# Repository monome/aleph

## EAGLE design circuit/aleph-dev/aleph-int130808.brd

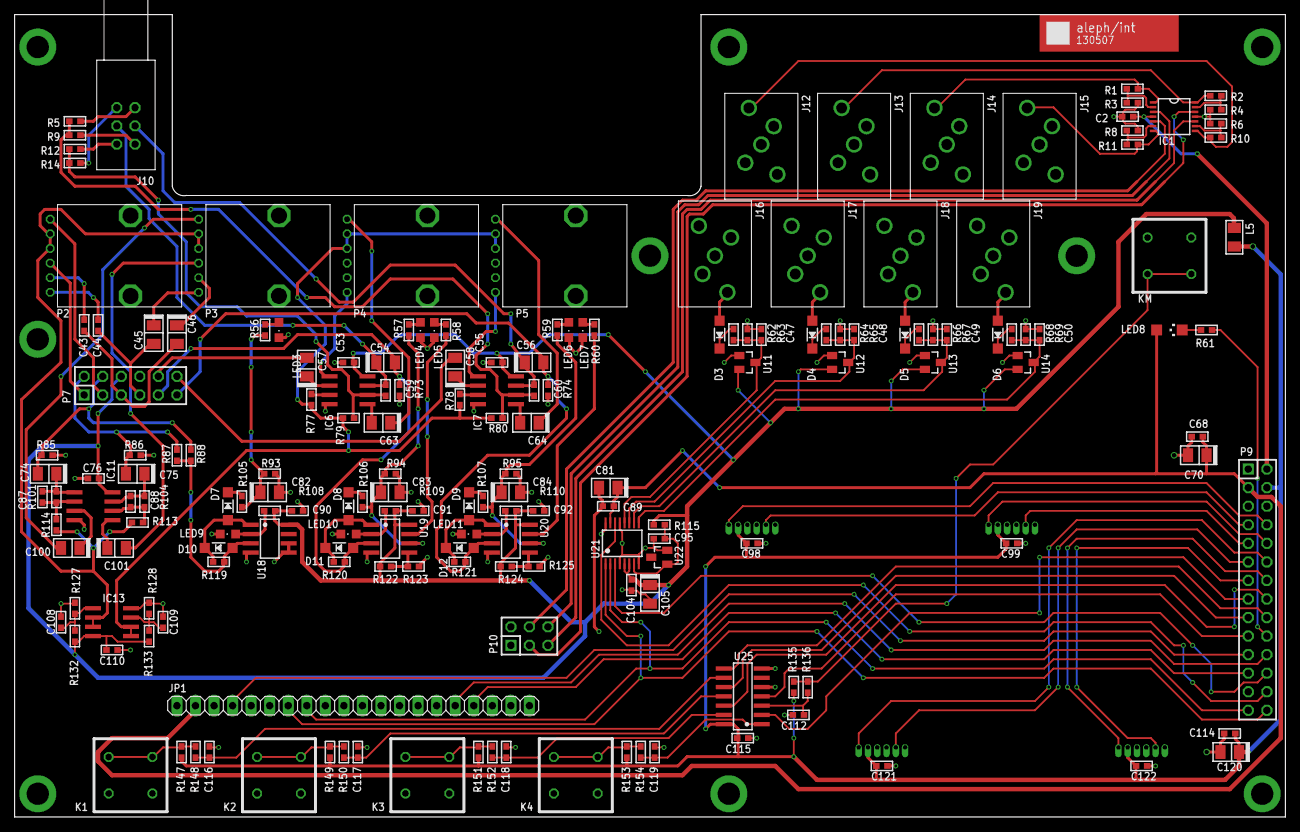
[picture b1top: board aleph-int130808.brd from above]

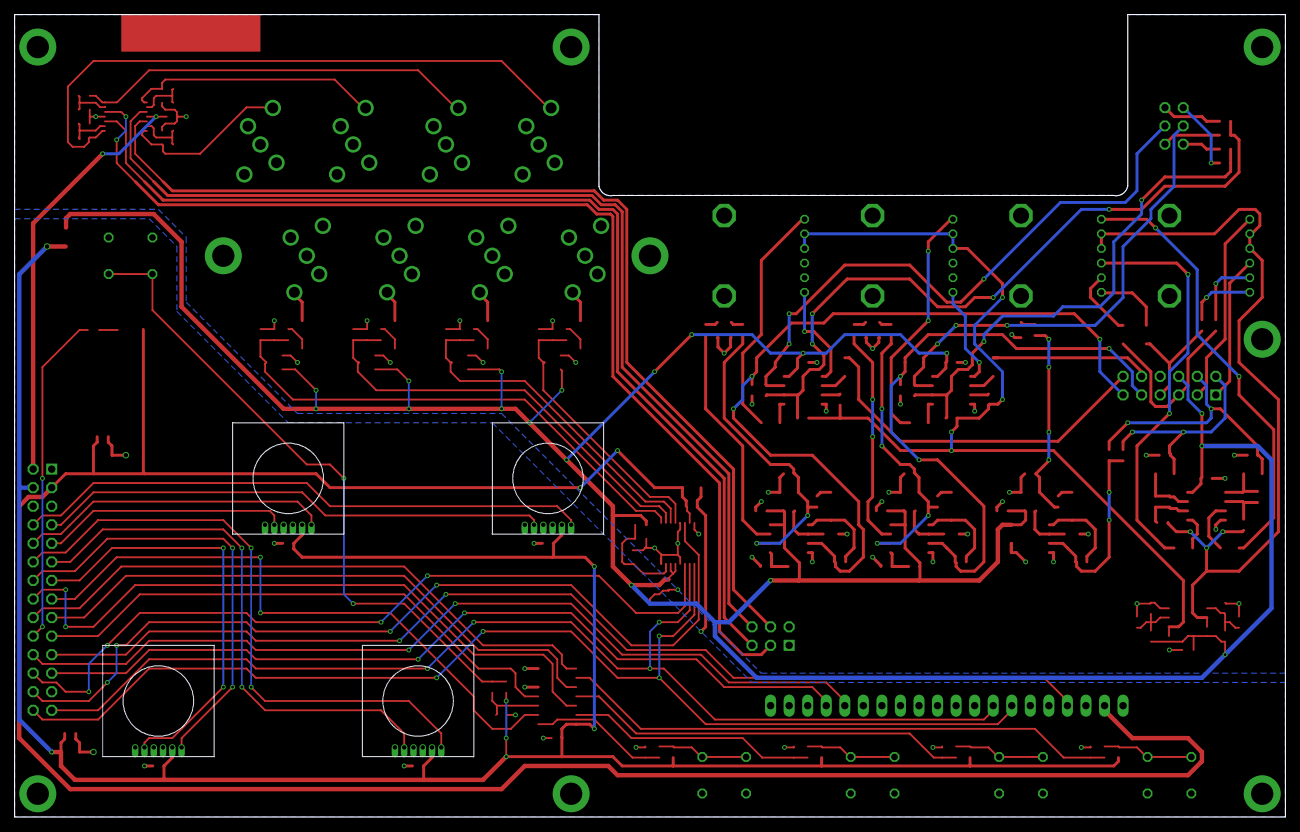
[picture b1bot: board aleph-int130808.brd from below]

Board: 4 copper layers, 174.0 x 109.9 mm, 196 parts (4 on the bottom side), 129 nets.

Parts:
C2, C53, C55, C68, C76, C89, C90, C91, C92, C95, C98, C99, C104, C108, C109, C110, C114, C115, C121, C122: 100n; C0603
C43, C44, C112, C116, C117, C118, C119: 1u; C0603
C45, C46, C54, C56, C57, C58, C63, C64, C70, C74, C75, C81, C82, C83, C84, C100, C101, C105, C120: 10u; C1206/T
C47, C48, C49, C50: 10n; C0603
C59, C60, C87, C88: 100p; C0603
D3, D4, D5, D6, D7, D8, D9, D10, D11, D12: 1N4148W-7; SOD123
E1, E2, E3, E4: BOURNS-EM14
H4, H5, H6, H7, H8, H9, H13, H14, H15: MOUNT440; 120-PAD-NS
IC1: AD8567; TSSOP14
IC6, IC7, IC11, IC13: AD8607R; SO8
J10: PHA2U
J12, J13, J14, J15, J16, J17, J18, J19: STX-3680
JP1: OLED; 1X20
K1, K2, K3, K4: PVA1
KM: PVA1
L5: 600; L1206
LED3, LED4, LED5, LED6, LED7, LED9, LED10, LED11: CHIPLED_0805
LED8: CHIPLED_1206
P2, P3, P4, P5: EVJ-POT
P7: M-2X06-DIL-100; DIL-100-2X06
P9: M-2X14-DIL-100; DIL-100-2X14
P10: M-2X03-DIL-100; DIL-100-2X03
R1, R2, R3, R4, R5, R6, R8, R10, R11, R14, R62, R63, R64, R65, R66, R67, R68, R69, R93, R94, R95, R101, R104, R108, R109, R110: 10k; R0603
R9, R12: 47k; R0603
R56, R57, R58, R59, R60, R105, R106, R107: 270; R0603
R61: 150; R0603
R73, R74, R85, R86, R123, R125, R127, R128, R132, R133: 100k; R0603
R77, R78, R119, R120, R121: 470k; R0603
R79, R80, R113, R114: 4k7; R0603
R87, R88, R115: 1k; R0603
R122, R124: 56k; R0603
R135, R147, R149, R151, R153: 82k; R0603
R136, R148, R150, R152, R154: 18k; R0603
REF-OLED: NHD-2.7
U11, U12, U13, U14: BAS70-04; SOT23
U18, U19, U20: TL072D; SO08
U21: AD7923; TSSOP16
U22: LM4040M3; SOT23
U25: 74HC14D; SO14

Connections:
+3V3: C68.2, C70.+, C81.+, C89.2, JP1.2, LED8.A, P9.3, U21.15
+5V: C98.2, C99.2, C114.2, C115.2, C120.+, C121.2, C122.2, E1.P$5, E2.P$5, E3.P$5, E4.P$5, L5.2, P9.4, R135.1, R147.1, R149.1, R151.1, R153.1, U25.14
+5VA: C53.2, C55.2, C76.2, C90.2, C91.2, C92.2, C104.2, C105.+, C110.2, IC6.8, IC7.8, IC11.8, IC13.8, L5.1, P7.6, R108.2, R109.2, R110.2, R115.1, R122.1, R124.1, R132.2, R133.2, U11.2, U12.2, U13.2, U14.2, U18.8, U19.8, U20.8, U21.5, U21.6
+12V: C2.1, IC1.4, P9.2
AGND: C2.2, C47.2, C48.2, C49.2, C50.2, C53.1, C55.1, C76.1, C82.-, C83.-, C84.-, C90.1, C91.1, C92.1, C95.1, C104.1, C105.-, C108.1, C109.1, C110.1, IC1.11, IC6.4, IC7.4, IC11.4, IC13.4, J12.5, J13.5, J14.5, J15.5, J16.3, J16.5, J17.3, J17.5, J18.3, J18.5, J19.3, J19.5, LED3.C, LED4.C, LED5.C, LED6.C, LED7.C, LED9.C, LED10.C, LED11.C, P7.8, P10.1, P10.2, R3.2, R4.2, R6.2, R8.2, R63.2, R65.2, R67.2, R69.2, R73.1, R74.1, R85.1, R86.1, R93.2, R94.2, R95.2, R123.2, R125.2, R127.1, R128.1, U11.1, U12.1, U13.1, U14.1, U18.4, U18.5, U18.6, U19.4, U20.4, U21.4, U21.8, U21.13, U21.16, U22.2
CVOUT1^: IC1.3, P10.6
CVOUT2^: IC1.5, P10.4
CVOUT3^: IC1.10, P10.5
CVOUT4^: IC1.12, P10.3
ENC0A^: E1.P$2, P9.13
ENC0B^: E1.P$6, P9.14
ENC1A^: E2.P$2, P9.11
ENC1B^: E2.P$6, P9.12
ENC2A^: E4.P$2, P9.9
ENC2B^: E4.P$6, P9.10
ENC3A^: E3.P$2, P9.7
ENC3B^: E3.P$6, P9.8
GAINL-1: C54.+, C59.1, IC6.7, J10._0
GAINL-2: C59.2, IC6.6, R12.1, R14.1, R79.2
GAINR-1: C56.+, C60.1, IC7.7, J10.0
GAINR-2: C60.2, IC7.6, R5.1, R9.1, R80.2
GND: C68.1, C70.-, C81.-, C89.1, C98.1, C99.1, C112.1, C114.1, C115.1, C116.1, C117.1, C118.1, C119.1, C120.-, C121.1, C122.1, E1.P$1, E2.P$1, E3.P$1, E4.P$1, JP1.1, JP1.5, JP1.6, JP1.10, JP1.11, JP1.12, JP1.13, JP1.14, JP1.19, JP1.20, K1.2, K1.3, K2.2, K2.3, K3.2, K3.3, K4.2, K4.3, KM.2, KM.3, P9.1, P9.5, P9.6, U25.5, U25.7
HPL^: P2.4, P7.1
HPR^: P2.1, P7.3
IN1L-J^: C57.-, P7.10
IN1L^: C54.-, D11.A, P7.9, R73.2, R120.2, U19.3
IN1R-J^: C58.-, P7.12
IN1R^: C56.-, D12.A, P7.11, R74.2, R121.2, U20.3
IN-VREF: IC13.1, IC13.2, P4.2, P4.3, P5.2, P5.3, R77.1, R78.1, R79.1, R80.1
KEY0^: P9.18, U25.8
KEY1^: P9.17, U25.10
KEY2^: P9.16, U25.12
KEY3^: P9.15, U25.2
MODE-KEY^: P9.19, U25.4
MODE-LED^: P9.20, R61.1
unnamed: IC1.2, R1.2, R3.1
unnamed: K1.1, K1.4, R147.2, R148.1
unnamed: C116.2, R148.2, U25.9
unnamed: K2.1, K2.4, R149.2, R150.1
unnamed: C117.2, R150.2, U25.11
unnamed: LED8.C, R61.2
unnamed: K3.1, K3.4, R151.2, R152.2
unnamed: C118.2, R152.1, U25.13
unnamed: K4.1, K4.4, R153.2, R154.2
unnamed: C119.2, R154.1, U25.1
unnamed: C45.+, P3.6
unnamed: D3.A, J16.4
unnamed: D4.C, R64.2
unnamed: D3.C, R62.2
unnamed: D5.C, R66.2
unnamed: C46.+, P3.5
unnamed: D4.A, J17.4
unnamed: KM.1, KM.4, R135.2, R136.2
unnamed: D6.C, R68.2
unnamed: C100.-, P3.1
unnamed: D5.A, J18.4
unnamed: C112.2, R136.1, U25.3
unnamed: C101.+, IC11.5
unnamed: D6.A, J19.4
unnamed: IC1.1, J14.4, R1.1
unnamed: C95.2, R115.2, U21.7, U22.1
unnamed: C75.+, C88.2, IC11.7, R104.2
unnamed: C88.1, IC11.6, R104.1, R113.2
unnamed: C101.-, P3.4
unnamed: C100.+, IC11.3
unnamed: C74.+, C87.2, IC11.1, R101.2
unnamed: C87.1, IC11.2, R101.1, R114.2
unnamed: C48.1, R64.1, R65.1, U12.3, U21.11
unnamed: C49.1, R66.1, R67.1, U13.3, U21.10
unnamed: C50.1, R68.1, R69.1, U14.3, U21.9
unnamed: C47.1, R62.1, R63.1, U11.3, U21.12
unnamed: IC1.6, R8.1, R11.2
unnamed: IC1.9, R6.1, R10.2
unnamed: IC1.13, R2.2, R4.1
unnamed: IC1.8, J12.4, R10.1
unnamed: IC1.14, J13.4, R2.1
unnamed: IC1.7, J15.4, R11.1
unnamed: C43.1, P2.5
unnamed: C44.1, P2.6
unnamed: C109.2, IC13.3, R128.2, R133.1
unnamed: IC6.3, R77.2
unnamed: IC6.1, P4.6
unnamed: C63.-, IC6.5
unnamed: D8.A, D11.C, R120.1, U19.1
unnamed: C108.2, IC13.5, R127.2, R132.1
unnamed: C57.+, IC6.2
unnamed: C63.+, P4.1
unnamed: D8.C, R106.2
unnamed: C83.+, R57.1, R94.1, R106.1, U19.6
unnamed: LED10.A, R109.1, U19.2
unnamed: IC7.3, R78.2
unnamed: J10._2, R12.2
unnamed: IC7.1, P5.6
unnamed: LED4.A, R57.2
unnamed: LED5.A, R58.2
unnamed: J10._1, R14.2
unnamed: J10.2, R9.2
unnamed: J10.1, R5.2
unnamed: R58.1, U19.7
unnamed: R122.2, R123.1, U19.5
unnamed: C64.-, IC7.5
unnamed: C58.+, IC7.2
unnamed: C64.+, P5.1
unnamed: D9.A, D12.C, R121.1, U20.1
unnamed: D9.C, R107.2
unnamed: C84.+, R59.1, R95.1, R107.1, U20.6
unnamed: LED11.A, R110.1, U20.2
unnamed: LED6.A, R59.2
unnamed: LED7.A, R60.2
unnamed: R60.1, U20.7
unnamed: R124.2, R125.1, U20.5
unnamed: D10.A, R87.1, R88.1, R119.2, U18.3
unnamed: D7.A, D10.C, R119.1, U18.1
unnamed: D7.C, R105.2
unnamed: C82.+, R56.1, R93.1, R105.1
unnamed: LED9.A, R108.1, U18.2
unnamed: LED3.A, R56.2
OLED-DC^: JP1.4, P9.21
OLED-RES^: JP1.16, P9.22
OUT1L-J^: C75.-, P7.2, R86.2, R87.2
OUT1L^: C43.2, C46.-, P7.5
OUT1R-J^: C74.-, P7.4, R85.2, R88.2
OUT1R^: C44.2, C45.-, P7.7
OUT-VREF: IC13.6, IC13.7, P2.2, P2.3, P3.2, P3.3, R113.1, R114.1
SPI1-CS0^: JP1.17, P9.23
SPI1-CS1^: P9.24, U21.3
SPI1-MISO^: P9.26, U21.14
SPI1-MOSI^: JP1.8, P9.27, U21.2
SPI1-SCK^: JP1.7, P9.28, U21.1

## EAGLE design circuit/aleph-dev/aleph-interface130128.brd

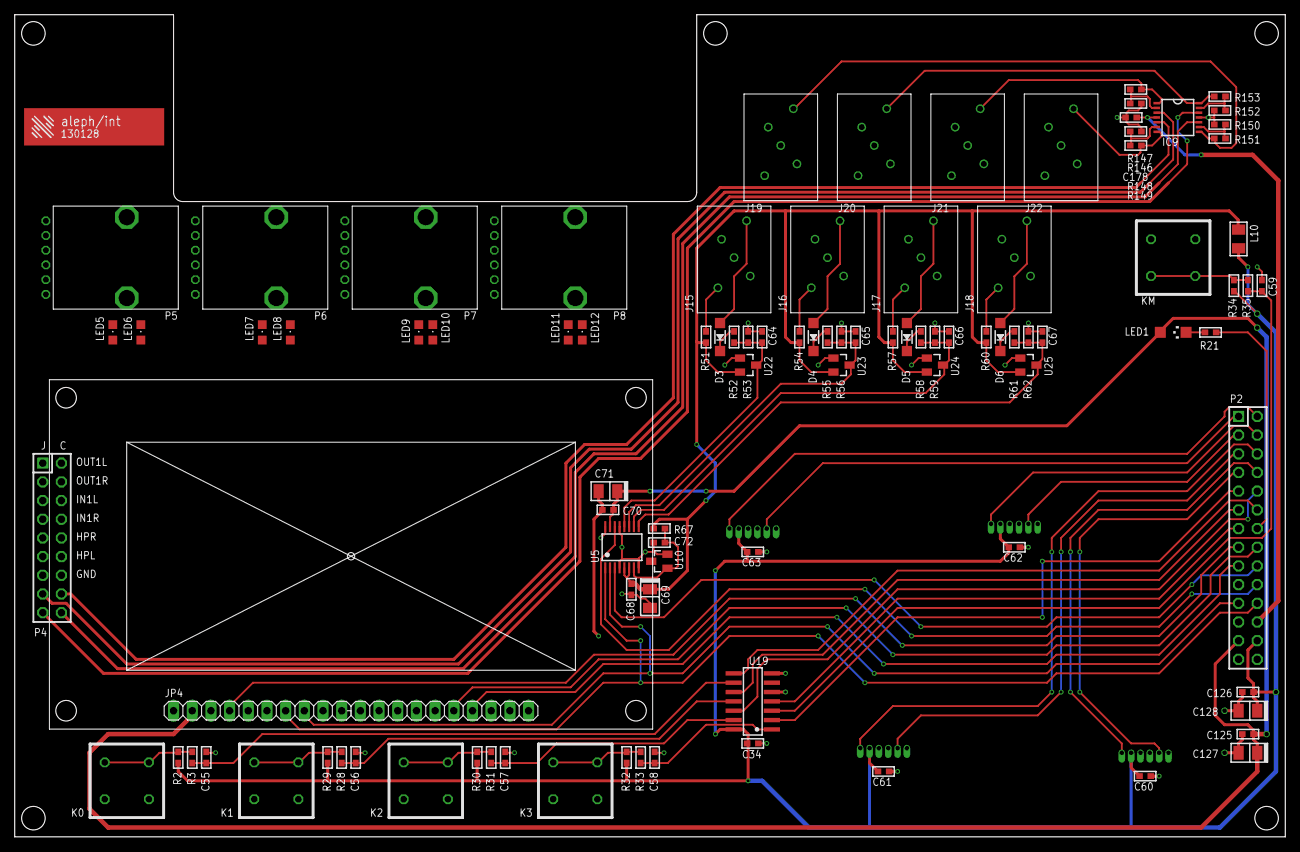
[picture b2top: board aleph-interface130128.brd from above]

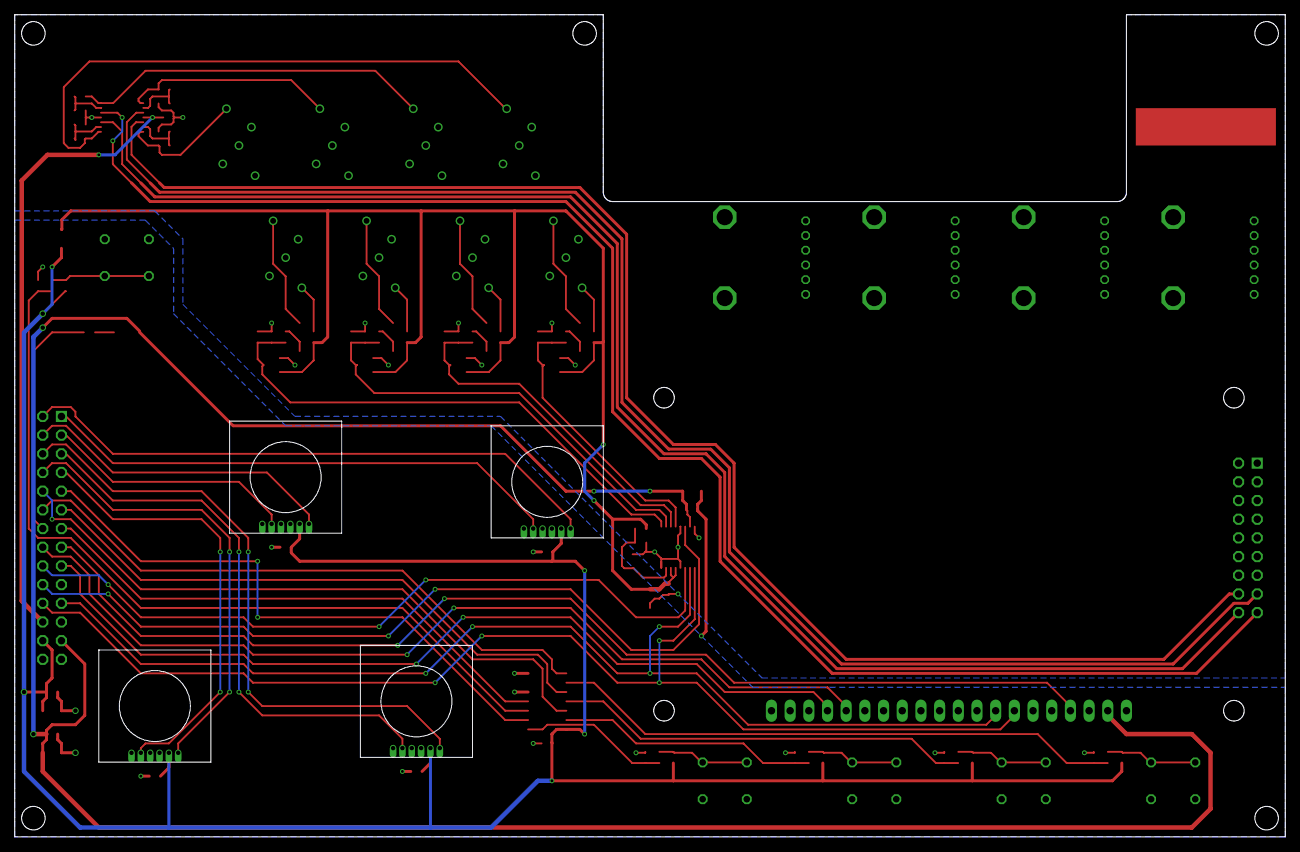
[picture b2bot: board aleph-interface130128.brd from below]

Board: 4 copper layers, 172.7 x 111.8 mm, 103 parts (4 on the bottom side), 67 nets.

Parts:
C34, C60, C61, C62, C63, C68, C70, C72, C125, C126, C178: 100n; C0603
C55, C56, C57, C58, C59: 1u; C0603
C64, C65, C66, C67: 10n; C0603
C69, C71, C127, C128: 10u; C1206/T
D3, D4, D5, D6: 1N4148W-7; SOD123
IC9: AD8567; TSSOP14
J15, J16, J17, J18, J19, J20, J21, J22: STX-3680
JP4: OLED; 1X20
K0, K1, K2, K3: PVA1
KM: PVA1
L10: 600; L1206
LED1: CHIPLED_1206
LED5, LED6, LED7, LED8, LED9, LED10, LED11, LED12: CHIPLED_0805
P2: M-2X14-DIL-100; DIL-100-2X14
P4: M-2X09-DIL-100; DIL-100-2X09
P5, P6, P7, P8: EVJ-POT
R2, R29, R30, R32, R34: 82k; R0603
R3, R28, R31, R33, R35: 18k; R0603
R21: 150; R0603
R51, R52, R53, R54, R55, R56, R57, R58, R59, R60, R61, R62, R146, R147, R148, R149, R150, R151, R152, R153: 10k; R0603
R67: 1k; R0603
U5: AD7923; TSSOP16
U10: LM4040M3; SOT23
U19: 74HC14D; SO14
U22, U23, U24, U25: BAS70-04; SOT23
U$2, U$3, U$4, U$5: BOURNS-EM14
U$10: NHD-2.7

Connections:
+3V3: C70.2, C71.+, C125.2, C127.+, JP4.2, LED1.A, P2.25, U5.15
+5V: C34.2, C60.2, C61.2, C62.2, C63.2, C126.2, C128.+, L10.2, P2.26, R2.1, R29.1, R30.1, R32.1, R34.1, U19.14, U$2.P$5, U$3.P$5, U$4.P$5, U$5.P$5
+5VA: C68.2, C69.+, L10.1, R51.2, R54.2, R57.2, R60.2, R67.1, U5.5, U5.6, U22.2, U23.2, U24.2, U25.2
+12V: C178.1, IC9.4, P2.24
AGND: C64.2, C65.2, C66.2, C67.2, C68.1, C69.-, C72.1, C178.2, IC9.11, J15.3, J15.5, J16.3, J16.5, J17.3, J17.5, J18.3, J18.5, J19.5, J20.5, J21.5, J22.5, P4.13, P4.14, R53.2, R56.2, R59.2, R62.2, R146.2, R148.2, R150.2, R152.2, U5.4, U5.8, U5.13, U5.16, U10.2, U22.1, U23.1, U24.1, U25.1
CVOUT1^: IC9.3, P4.15
CVOUT2^: IC9.5, P4.16
CVOUT3^: IC9.10, P4.18
CVOUT4^: IC9.12, P4.17
ENC0A^: P2.7, U$2.P$2
ENC0B^: P2.8, U$2.P$6
ENC1A^: P2.5, U$3.P$2
ENC1B^: P2.6, U$3.P$6
ENC2A^: P2.3, U$4.P$2
ENC2B^: P2.4, U$4.P$6
ENC3A^: P2.1, U$5.P$2
ENC3B^: P2.2, U$5.P$6
GND: C34.1, C55.1, C56.1, C57.1, C58.1, C59.1, C60.1, C61.1, C62.1, C63.1, C70.1, C71.-, C125.1, C126.1, C127.-, C128.-, JP4.1, JP4.5, JP4.6, JP4.10, JP4.11, JP4.12, JP4.13, JP4.14, JP4.19, JP4.20, K0.2, K0.3, K1.2, K1.3, K2.2, K2.3, K3.2, K3.3, KM.2, KM.3, P2.23, P2.27, P2.28, U19.5, U19.7, U$2.P$1, U$3.P$1, U$4.P$1, U$5.P$1
KEY0^: P2.12, U19.8
KEY1^: P2.11, U19.10
KEY2^: P2.10, U19.12
KEY3^: P2.9, U19.2
MODE-KEY^: P2.13, U19.4
MODE-LED^: P2.14, R21.1
unnamed: IC9.2, R146.1, R147.2
unnamed: K0.1, K0.4, R2.2, R3.1
unnamed: C55.2, R3.2, U19.9
unnamed: K1.1, K1.4, R28.1, R29.2
unnamed: C56.2, R28.2, U19.11
unnamed: LED1.C, R21.2
unnamed: K2.1, K2.4, R30.2, R31.2
unnamed: C57.2, R31.1, U19.13
unnamed: K3.1, K3.4, R32.2, R33.2
unnamed: C58.2, R33.1, U19.1
unnamed: J17.1, R57.1
unnamed: D3.A, J15.4
unnamed: D4.C, R55.2
unnamed: D3.C, R52.2
unnamed: D5.C, R58.2
unnamed: J16.1, R54.1
unnamed: D4.A, J16.4
unnamed: KM.1, KM.4, R34.2, R35.2
unnamed: D6.C, R61.2
unnamed: J15.1, R51.1
unnamed: D5.A, J17.4
unnamed: C59.2, R35.1, U19.3
unnamed: J18.1, R60.1
unnamed: D6.A, J18.4
unnamed: IC9.1, J21.4, R147.1
unnamed: C72.2, R67.2, U5.7, U10.1
unnamed: C65.1, R55.1, R56.1, U5.11, U23.3
unnamed: C66.1, R58.1, R59.1, U5.10, U24.3
unnamed: C67.1, R61.1, R62.1, U5.9, U25.3
unnamed: C64.1, R52.1, R53.1, U5.12, U22.3
unnamed: IC9.6, R148.1, R149.2
unnamed: IC9.9, R150.1, R151.2
unnamed: IC9.13, R152.1, R153.2
unnamed: IC9.8, J19.4, R151.1
unnamed: IC9.14, J20.4, R153.1
unnamed: IC9.7, J22.4, R149.1
OLED-DC^: JP4.4, P2.15
OLED-RES^: JP4.16, P2.16
SPI1-CS0^: JP4.17, P2.17
SPI1-CS1^: P2.18, U5.3
SPI1-MISO^: P2.20, U5.14
SPI1-MOSI^: JP4.8, P2.21, U5.2
SPI1-SCK^: JP4.7, P2.22, U5.1

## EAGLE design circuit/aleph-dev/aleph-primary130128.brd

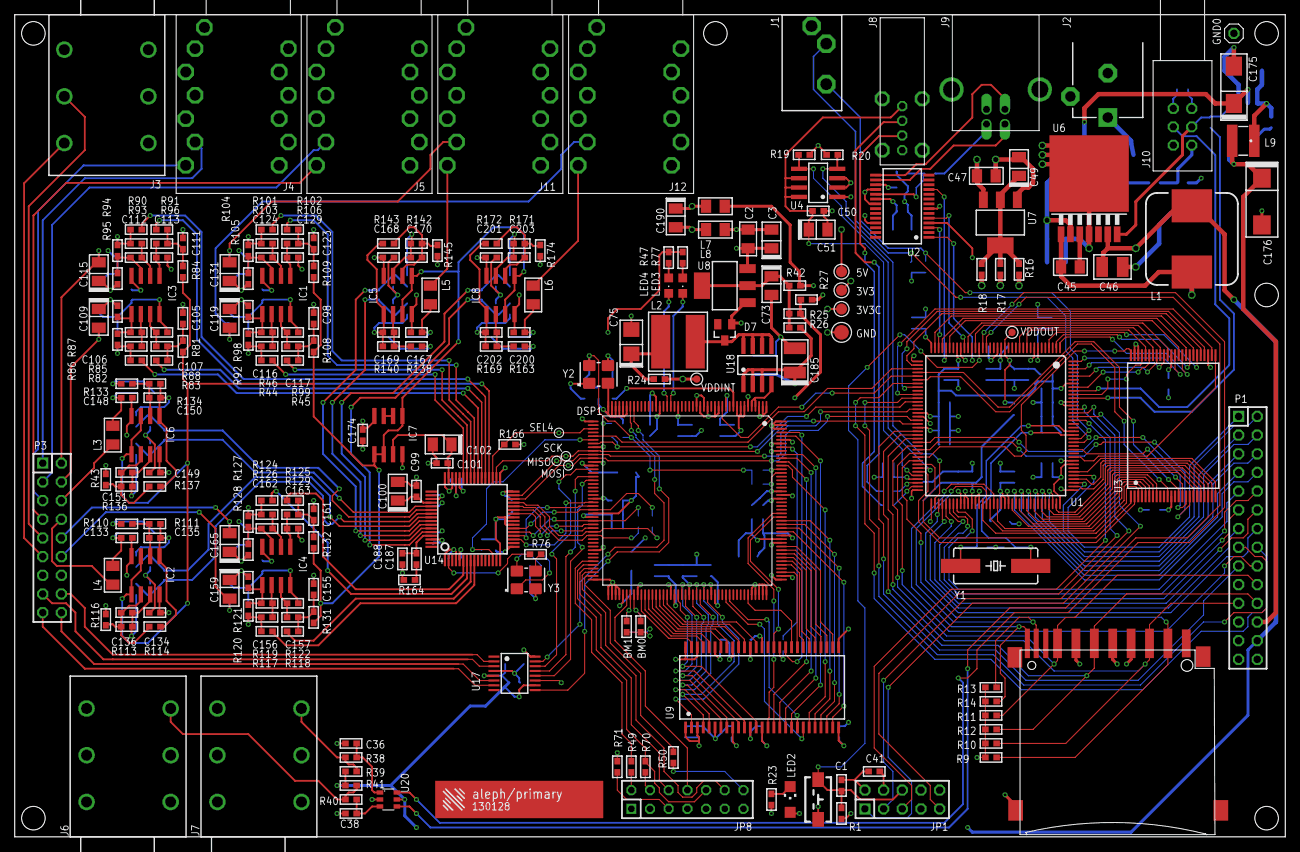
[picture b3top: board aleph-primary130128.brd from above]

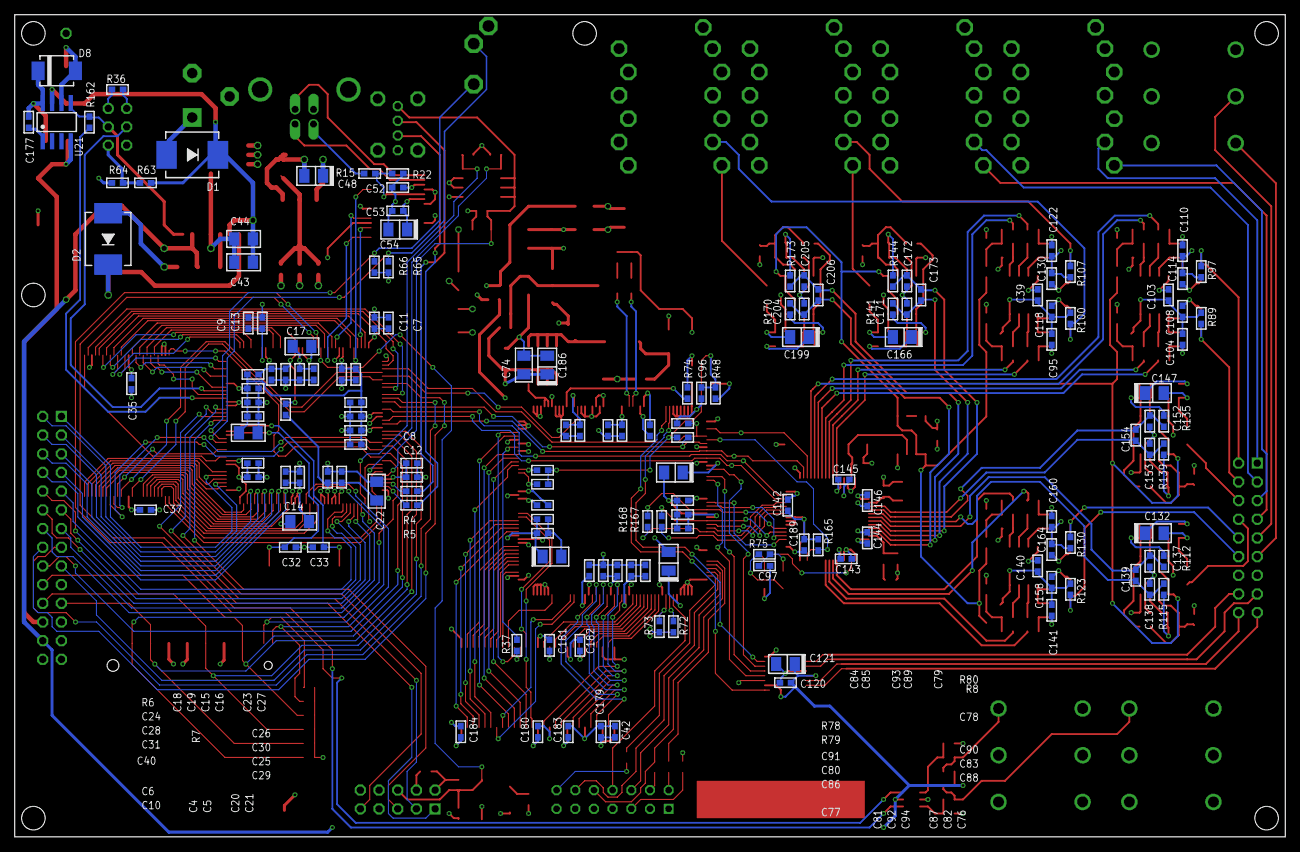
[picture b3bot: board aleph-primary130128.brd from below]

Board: 4 copper layers, 172.7 x 111.8 mm, 374 parts (152 on the bottom side), 317 nets.

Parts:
3V3, 3V3C, 5V: TPS-SMD-15R; SMD-15R
BM0: 0; R0603
BM1: DNP; R0603
C1, C4, C6, C7, C8, C9, C16, C31, C39, C41, C50, C52, C53, C79, C80, C81, C82, C83, C84, C89, C90, C91, C92, C99, C101, C103, C120, C134, C140, C142, C143, C144, C145, C146, C149, C168, C174, C189, C201: 100n; C0603
C2, C47, C74: 100n; C1206
C3, C48, C49, C73, C76, C77, C78, C102, C109, C115, C119, C121, C131, C159, C165, C186, C190: 10u; C1206/T
C5, C10, C11, C12, C13, C15, C21, C27, C28, C29, C30: 33n; C0603
C14, C17: 4.7u; C1206
C18: 2.2u; C0603
C19: 470p; C0603
C20, C23, C24, C25, C26: 2.7n; C0603
C22, C40: 2.2u; C1206
C32, C33: 18p; C0603
C35, C37, C42, C85, C86, C87, C88, C93, C94, C96, C97, C177, C179, C180, C181, C182, C183, C184: 10n; C0603
C36, C38: 1u; C0603
C43: 22u; C1206
C44: 470n; C1206
C45: 10n; C1206
C46: 47u; C3225
C51, C54, C132, C147, C166, C199: 4.7u; C1206/T
C75: 100u; C3528/T
C95, C104, C110, C122, C141, C160: 330p; C0603
C98, C105, C111, C123, C155, C161: 680p; C0603
C100: 47u; C1206/T
C106, C112, C116, C124, C133, C139, C148, C154, C156, C162, C167, C173, C200, C206: 100p; C0603
C107, C113, C117, C129, C157, C163: 220p; C0603
C108, C114, C118, C130, C158, C164: 2200p; C0603
C135, C136, C150, C151, C169, C170, C202, C203: 120p; C0603
C137, C138, C152, C153, C171, C172, C204, C205: 1n; C0603
C175: 15u; C6032/T
C176: 68u; C7343/T
C185: 100u; C1210/T
C187: 5600p; C0603
C188: 390p; C0603
D1, D2: MBRS360T3; SMC
D7: zhcs1000; SOT23
D8: MBRS130LT3; SMB403A
DSP1: BF533; LQFP176
GND: TPS-SMD-20R; SMD-20R
GND0: 1X01
IC1, IC2, IC3, IC4, IC5, IC6, IC8: AD8606; SO8
IC7: AD8607R; SO8
J1: SJ1-3533NG
J2: PJ-102AH/BH; PJ-102XH
J3, J6, J7: STEREOSW2GND; NEUTRIK-NRJ6HM-1
J4, J5, J11, J12: NSJ12HF
J8: USBA-VERT
J9: USB_B
J10: PHA2U
JP1: AVR-JTAG; AVR-JTAG-10
JP8: JPQ-07-100; JPQ-07
L1: MSS1278
L2: SRR6038-100Y; SRR6038
L3, L4, L5, L6, L7, L8: 600; L1206
L9: LPS4018-68uh; LPS4018
LED2: CHIPLED_1206
LED3, LED4: CHIPLED_0805
P1: M-2X14-DIL-100; DIL-100-2X14
P3: M-2X09-DIL-100; DIL-100-2X09
R1, R22, R48, R65, R66, R72, R73, R75, R78, R79, R80, R165: 10k; R0603
R4, R5: 39; R0603
R6, R7, R16, R17, R18, R24, R25, R26, R42, R49, R50, R167, R168: 0; R0603
R8, R9, R10, R11, R12, R13, R14, R36, R64, R162, R166: 100k; R0603
R15: 4.7k; R0603
R19, R20: 47k; R0603
R23, R47, R77: 150; R0603
R27: 3.32k; R0603
R37: 22; R0603
R38, R40: 18k; R0603
R39, R41: 82k; R0603
R43, R116, R145, R174: 750k; R0603
R44, R82, R90, R101, R117, R124: 11k; R0603
R45, R83, R86, R91, R92, R94, R102, R104, R118, R120, R125, R127: 5k49; R0603
R46, R85, R93, R103, R119, R126: 3k32; R0603
R63: 330k; R0603
R70, R71: 4k7; R0603
R74, R76: 33; R0603
R81, R84, R108, R109, R131, R132: 2k74; R0603
R87, R95, R98, R105, R121, R128: 604; R0603
R88, R96, R99, R106, R122, R129: 1k65; R0603
R89, R97, R100, R107, R123, R130: 49k9; R0603
R110, R111, R113, R114, R133, R134, R136, R137, R138, R140, R142, R143, R163, R169, R171, R172: 5k76; R0603
R112, R115, R135, R139, R141, R144, R170, R173: 237; R0603
R164: 562; R0603
U1: AT32UC3A0512; LQFP144
U2: FT232RL; SSOP28
U3: CY62167EV30-Z; TSOP48
U4: TPS2020; SO08
U6: LM2678; TO263-7
U7, U8: ADP3339; SOT223
U9: MT48LC32M16A2tg-75; TSOP54
U14: AD1939; SQFP-S-10X10-64
U17: AD5686R; TSSOP16
U18: FDS9431A; SO08
U20: SN74LVC2G14; SOT23-6
U21: LM2674; SO08
U$1: PANASONIC-EVQ
U$6: SDMMC06132; 06132
VDDINT: TPS-SMD-10R; SMD-10R
VDDOUT: TPS-SMD-10R; SMD-10R
Y1: 12mhz; HC49UP@1
Y2: ASFL1-27mhz; ASFL1
Y3: ASFL1-12.288mhz; ASFL1

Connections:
+3V3: 3V3.TP, C35.1, C37.1, C41.1, JP1.4, LED2.A, P1.25, R1.2, R9.2, R10.2, R11.2, R12.2, R13.2, R14.2, R18.1, R65.1, R66.1, U2.4, U3.12, U3.37, U$6.4
+3V3A: C39.2, C103.2, C134.2, C140.2, C143.1, C144.1, C145.1, C146.1, C149.2, C168.2, C174.2, C188.1, C190.+, C201.2, IC1.8, IC2.8, IC3.8, IC4.8, IC5.8, IC6.8, IC7.8, IC8.8, L7.1, R164.2, U14.5, U14.45, U14.51, U14.62
+3V3C: 3V3C.TP, C42.2, C96.1, C97.1, C142.1, C179.2, C180.2, C181.2, C182.2, C183.2, C184.2, C189.1, L7.2, R8.2, R42.1, R47.2, R48.2, R71.1, R72.2, R73.2, R75.2, R77.2, R78.2, R79.2, R166.1, U9.1, U9.3, U9.9, U9.14, U9.27, U9.43, U9.49, U14.17, U14.32, U17.11, Y2.4, Y3.4
+5V: 5V.TP, C2.2, C3.+, C46.1, C47.2, C48.+, C53.2, C54.+, C120.1, C121.+, L1.2, P1.26, R19.2, R20.2, R39.1, R41.1, U2.20, U4.2, U4.3, U6.6, U7.3, U8.3, U17.5, U17.10, U20.5
+12V: C176.+, L9.2, P1.24, U21.4
A-A1: U1.118, U3.25
A-A2: U1.114, U3.24
A-A3: U1.112, U3.23
A-A4: U1.110, U3.22
A-A5: U1.107, U3.21
A-A6: U1.105, U3.20
A-A7: U1.103, U3.19
A-A8: U1.101, U3.18
A-A9: U1.99, U3.8
A-A10: U1.97, U3.7
A-A11: U1.95, U3.6
A-A12: U1.91, U3.5
A-A13: U1.89, U3.4
A-A14: U1.87, U3.3
A-A15: U1.67, U3.2
A-A16: U1.65, U3.1
A-A17: U1.63, U3.48
A-A18: U1.61, U3.17
A-A19: U1.59, U3.16
A-D0: U1.38, U3.29
A-D1: U1.35, U3.31
A-D2: U1.33, U3.33
A-D3: U1.31, U3.35
A-D4: U1.26, U3.38
A-D5: U1.24, U3.40
A-D6: U1.12, U3.42
A-D7: U1.10, U3.44
A-D8: U1.4, U3.30
A-D9: U1.2, U3.32
A-D10: U1.1, U3.34
A-D11: U1.144, U3.36
A-D12: U1.142, U3.39
A-D13: U1.140, U3.41
A-D14: U1.137, U3.43
A-D15: U1.135, U3.45
A-RESET: C1.1, JP1.6, R1.1, U1.23, U$1.2
A-TCK: JP1.1, U1.129
A-TDI: JP1.9, U1.131
A-TDO: JP1.3, U1.130
A-TMS: JP1.5, U1.128
ABE0_: DSP1.P$151, U9.15
ABE1_: DSP1.P$150, U9.39
AD1939_RESET: DSP1.P$50, R165.1, U14.14
AGND: C39.1, C95.1, C98.2, C99.1, C100.-, C101.1, C102.-, C103.1, C104.1, C105.2, C107.1, C108.1, C110.1, C111.2, C113.1, C114.1, C117.1, C118.1, C120.2, C121.-, C122.1, C123.2, C129.1, C130.1, C133.1, C134.1, C137.2, C138.1, C140.1, C141.1, C143.2, C144.2, C145.2, C146.2, C148.1, C149.1, C152.2, C153.1, C155.2, C157.1, C158.1, C160.1, C161.2, C163.1, C164.1, C167.1, C168.1, C171.2, C172.1, C174.1, C190.-, C200.1, C201.1, C204.2, C205.1, IC1.4, IC2.4, IC3.4, IC4.4, IC5.4, IC6.4, IC7.4, IC8.4, J3.RN, J3.S, J3.TN, J4.G, J4.RNB, J4.RNT, J4.SB, J4.SNB, J4.SNT, J4.ST, J4.TNB, J4.TNT, J5.G, J5.RNB, J5.RNT, J5.SB, J5.SNB, J5.SNT, J5.ST, J5.TNB, J5.TNT, J11.RNB, J11.RNT, J11.SB, J11.SNB, J11.SNT, J11.ST, J11.TNB, J11.TNT, J12.G, J12.RNB, J12.RNT, J12.SB, J12.SNB, J12.SNT, J12.ST, J12.TNB, J12.TNT, L8.1, P3.13, P3.14, R43.2, R89.2, R97.2, R100.2, R107.2, R116.2, R123.2, R130.2, R145.2, R174.2, U14.1, U14.4, U14.44, U14.46, U14.48, U17.4, U17.16
B-A1: DSP1.P$149, U9.23
B-A2: DSP1.P$148, U9.24
B-A3: DSP1.P$147, U9.25
B-A4: DSP1.P$146, U9.26
B-A5: DSP1.P$142, U9.29
B-A6: DSP1.P$141, U9.30
B-A7: DSP1.P$140, U9.31
B-A8: DSP1.P$139, U9.32
B-A9: DSP1.P$138, U9.33
B-A10: DSP1.P$137, U9.34
B-A12: DSP1.P$135, U9.35
B-A13: DSP1.P$127, U9.36
B-A18: DSP1.P$122, U9.20
B-A19: DSP1.P$121, U9.21
B-D0: DSP1.P$116, U9.2
B-D1: DSP1.P$115, U9.4
B-D2: DSP1.P$114, U9.5
B-D3: DSP1.P$113, U9.7
B-D4: DSP1.P$112, U9.8
B-D5: DSP1.P$110, U9.10
B-D6: DSP1.P$109, U9.11
B-D7: DSP1.P$108, U9.13
B-D8: DSP1.P$105, U9.42
B-D9: DSP1.P$104, U9.44
B-D10: DSP1.P$103, U9.45
B-D11: DSP1.P$102, U9.47
B-D12: DSP1.P$101, U9.48
B-D13: DSP1.P$100, U9.50
B-D14: DSP1.P$99, U9.51
B-D15: DSP1.P$98, U9.53
B-HWAIT: DSP1.P$49, R80.2, U1.39
B-MISO: DSP1.P$54, U1.50, U14.31
B-MOSI: DSP1.P$55, U1.53, U14.30
B-RESET: DSP1.P$13, U1.41
B-SCK: DSP1.P$53, U1.54, U14.34
B-SPISEL4: DSP1.P$47, R166.2, U14.35
B-SPISS: DSP1.P$51, R8.1, U1.48
BMODE0: BM0.2, DSP1.P$96, R73.1
BMODE1: BM1.2, DSP1.P$95, R72.1
CLKIN: DSP1.P$10, R74.1
CLKOUT: DSP1.P$169, R37.2
CS1: U1.46, U3.26
CVOUT1: P3.15, U17.3
CVOUT2: P3.16, U17.2
CVOUT3: P3.18, U17.6
CVOUT4: P3.17, U17.7
DAC-LDAC: DSP1.P$37, U17.9
DAC-RESET: DSP1.P$38, U17.15
DM: J8.2, R4.2
DP: J8.3, R5.2
DR0PRI: DSP1.P$74, U14.27
DR0SEC: DSP1.P$73, U14.26
DT0PRI: DSP1.P$68, U14.20
DT0SEC: DSP1.P$67, U14.19
DT1SEC: DSP1.P$58, U17.14
EMU_: DSP1.P$83, R49.1
ENC0A: P1.7, U1.98
ENC0B: P1.8, U1.96
ENC1A: P1.5, U1.102
ENC1B: P1.6, U1.100
ENC2A: P1.3, U1.106
ENC2B: P1.4, U1.104
ENC3A: P1.1, U1.113
ENC3B: P1.2, U1.111
FTDI-CTS: U1.34, U2.3
FTDI-RTS: U1.32, U2.11
FTDI-RX: U1.25, U2.1
FTDI-TX: U1.27, U2.5
GND: BM0.1, BM1.1, C1.2, C2.1, C3.-, C4.2, C5.2, C6.2, C7.2, C8.2, C9.2, C10.2, C11.2, C12.2, C13.2, C14.2, C15.2, C16.2, C17.2, C18.2, C19.2, C20.2, C21.2, C22.2, C23.2, C24.2, C25.2, C26.2, C27.2, C28.2, C29.2, C30.2, C31.2, C32.2, C33.2, C35.2, C36.1, C37.2, C38.1, C40.2, C41.2, C42.1, C43.1, C44.1, C46.2, C47.1, C48.-, C49.-, C50.1, C51.-, C52.1, C53.1, C54.-, C73.-, C74.1, C75.-, C76.-, C77.-, C78.-, C79.1, C80.1, C81.1, C82.1, C83.1, C84.1, C85.1, C86.1, C87.1, C88.1, C89.1, C90.1, C91.1, C92.1, C93.1, C94.1, C96.2, C97.2, C142.2, C175.-, C176.-, C179.1, C180.1, C181.1, C182.1, C183.1, C184.1, C185.-, C186.-, C189.2, D2.A, D7.1, D8.A, DSP1.P$1, DSP1.P$2, DSP1.P$3, DSP1.P$7, DSP1.P$8, DSP1.P$9, DSP1.P$14, DSP1.P$15, DSP1.P$17, DSP1.P$19, DSP1.P$30, DSP1.P$39, DSP1.P$40, DSP1.P$41, DSP1.P$42, DSP1.P$43, DSP1.P$44, DSP1.P$56, DSP1.P$70, DSP1.P$88, DSP1.P$89, DSP1.P$90, DSP1.P$91, DSP1.P$92, DSP1.P$97, DSP1.P$106, DSP1.P$117, DSP1.P$128, DSP1.P$129, DSP1.P$130, DSP1.P$131, DSP1.P$132, DSP1.P$133, DSP1.P$144, DSP1.P$155, DSP1.P$170, DSP1.P$174, DSP1.P$175, DSP1.P$176, GND.TP, GND0.1, J1.1, J2.2, J6.R, J6.RN, J6.S, J6.TN, J7.R, J7.RN, J7.S, J7.TN, J8.4, J8.G1, J8.G2, J8.G3, J8.G4, J9.GND, J10._1, JP1.2, JP1.10, JP8.1, JP8.4, JP8.7, JP8.9, JP8.11, JP8.13, L8.2, P1.23, P1.27, P1.28, R22.2, R23.1, R27.2, R36.2, R64.2, R70.2, R80.1, R165.2, U1.8, U1.18, U1.28, U1.37, U1.52, U1.72, U1.73, U1.82, U1.83, U1.85, U1.86, U1.94, U1.109, U1.117, U1.132, U1.133, U2.7, U2.18, U2.21, U2.25, U3.27, U3.46, U3.47, U4.1, U6.4, U6.8, U7.1, U8.1, U9.6, U9.12, U9.28, U9.41, U9.46, U9.52, U9.54, U14.16, U14.23, U14.24, U14.25, U14.33, U20.2, U21.6, U$1.1, U$6.3, U$6.6, U$6.GP, Y2.2, Y3.2
HBE: U1.40, U3.14
HP-L: J3.R, P3.9
HP-LP: C165.-, P3.10, R130.1
HP-R: J3.T, P3.11
HP-RP: C159.-, P3.12, R123.1
HPL+: R125.2, U14.6
HPL-: R124.2, U14.7
HPR+: R118.2, U14.8
HPR-: R117.2, U14.9
IN1-L: J4.TT, P3.5
IN1-LP: L3.2, P3.6
IN1-R: J5.TT, P3.7
IN1-RP: L4.2, P3.8
IN1L+: C153.2, C154.2, R139.1, U14.53
IN1L-: C152.1, C154.1, R135.1, U14.54
IN1R+: C138.2, C139.2, R115.1, U14.55
IN1R-: C137.1, C139.1, R112.1, U14.56
IN2-L: J11.TT, L5.2
IN2-R: J12.TT, L6.2
IN2L+: C172.2, C173.2, R144.1, U14.57
IN2L-: C171.1, C173.1, R141.1, U14.58
IN2R+: C205.2, C206.2, R173.1, U14.59
IN2R-: C204.1, C206.1, R170.1, U14.60
KEY0: P1.12, U1.77
KEY1: P1.11, U1.78
KEY2: P1.10, U1.79
KEY3: P1.9, U1.80
LBE: U1.120, U3.15
MMC-DETECT: R13.1, U1.88, U$6.CD
MMC-PROTECT: R14.1, U1.90, U$6.WP
MODE-KEY: P1.13, U1.76
MODE-LED: P1.14, U1.75
unnamed: D1.A, J2.1
unnamed: C32.1, U1.124, Y1.2
unnamed: C33.1, U1.125, Y1.1
unnamed: R15.1, R22.1, U2.19
unnamed: C45.1, D2.C, L1.1, U6.1
unnamed: C45.2, U6.3
unnamed: J9.DM, U2.16
unnamed: J9.DP, U2.15
unnamed: C52.2, U2.17
unnamed: LED2.C, R23.2
unnamed: C73.+, R25.2, R26.2, R42.2, U8.2, U8.4
unnamed: J9.VCC, R15.2
unnamed: C74.2, C185.+, C186.+, R26.1, U18.1, U18.2, U18.3
unnamed: D7.3, L2.1, U18.5, U18.6, U18.7, U18.8
unnamed: C75.+, L2.2, R24.2
unnamed: R37.1, U9.38
unnamed: R48.1, Y2.1
unnamed: JP8.2, R49.2
unnamed: JP8.5, R71.2
unnamed: DSP1.P$163, R78.1
unnamed: JP8.14, R50.2
unnamed: C49.+, R16.2, R17.2, R18.2, U7.2, U7.4
unnamed: DSP1.P$162, R79.1
unnamed: R75.1, Y3.1
unnamed: R74.2, Y2.3
unnamed: R4.1, U1.70
unnamed: R5.1, U1.71
unnamed: J10.1, R36.1
unnamed: C147.+, R133.2
unnamed: C38.2, R40.2, U20.3
unnamed: J10.2, R63.1, R64.1
unnamed: R76.2, Y3.3
unnamed: R76.1, U14.2
unnamed: DSP1.P$27, LED3.C
unnamed: C101.2, C102.+, IC7.3, U14.47
unnamed: C99.2, C100.+, U14.52
unnamed: C187.2, C188.2, U14.61
unnamed: DSP1.P$28, LED4.C
unnamed: C187.1, R164.1
unnamed: LED3.A, R77.1
unnamed: LED4.A, R47.1
unnamed: C104.2, R82.1, R85.2, R86.2
unnamed: C105.1, R81.1, R83.1, R88.1
unnamed: C107.2, IC3.3, R88.2
unnamed: C106.2, IC3.1, R86.1, R87.1
unnamed: C108.2, C109.+, R87.2
unnamed: C110.2, R90.1, R93.2, R94.2
unnamed: C106.1, IC3.2, R85.1
unnamed: C111.1, R84.1, R91.1, R96.1
unnamed: C113.2, IC3.5, R96.2
unnamed: C112.2, IC3.7, R94.1, R95.1
unnamed: C114.2, C115.+, R95.2
unnamed: C112.1, IC3.6, R93.1
unnamed: C95.2, R44.1, R46.2, R92.2
unnamed: C98.1, R45.1, R99.1, R108.1
unnamed: C117.2, IC1.3, R99.2
unnamed: C116.2, IC1.1, R92.1, R98.1
unnamed: C118.2, C119.+, R98.2
unnamed: C116.1, IC1.2, R46.1
unnamed: C122.2, R101.1, R103.2, R104.2
unnamed: C123.1, R102.1, R106.1, R109.1
unnamed: C129.2, IC1.5, R106.2
unnamed: C124.2, IC1.7, R104.1, R105.1
unnamed: C130.2, C131.+, R105.2
unnamed: C124.1, IC1.6, R103.1
unnamed: C135.1, IC2.1, R111.1, R112.2, R114.2
unnamed: C136.1, IC2.7, R113.1, R115.2
unnamed: C132.-, C133.2, L4.1
unnamed: C135.2, IC2.2, R110.1, R111.2
unnamed: C136.2, IC2.6, R113.2, R114.1, R116.1
unnamed: C132.+, R110.2
unnamed: C141.2, R117.1, R119.2, R120.2
unnamed: C155.1, R118.1, R122.1, R131.1
unnamed: C150.1, IC6.1, R134.1, R135.2, R137.2
unnamed: C151.1, IC6.7, R136.1, R139.2
unnamed: C147.-, C148.2, L3.1
unnamed: C157.2, IC4.3, R122.2
unnamed: C150.2, IC6.2, R133.1, R134.2
unnamed: C156.2, IC4.1, R120.1, R121.1
unnamed: C151.2, IC6.6, R43.1, R136.2, R137.1
unnamed: C158.2, C159.+, R121.2
unnamed: C156.1, IC4.2, R119.1
unnamed: C160.2, R124.1, R126.2, R127.2
unnamed: C161.1, R125.1, R129.1, R132.1
unnamed: C163.2, IC4.5, R129.2
unnamed: C162.2, IC4.7, R127.1, R128.1
unnamed: C164.2, C165.+, R128.2
unnamed: C162.1, IC4.6, R126.1
unnamed: C169.1, IC5.1, R140.1, R141.2, R143.2
unnamed: C36.2, R38.2, U20.1
unnamed: C170.1, IC5.7, R142.1, R144.2
unnamed: C166.-, C167.2, L5.1
unnamed: C169.2, IC5.2, R138.1, R140.2
unnamed: C170.2, IC5.6, R142.2, R143.1, R145.1
unnamed: C166.+, R138.2
unnamed: IC7.6, IC7.7
unnamed: C177.1, U21.1
unnamed: C177.2, D8.C, L9.1, U21.8
unnamed: C202.1, IC8.1, R169.1, R170.2, R172.2
unnamed: C203.1, IC8.7, R171.1, R173.2
unnamed: C199.-, C200.2, L6.1
unnamed: C202.2, IC8.2, R163.1, R169.2
unnamed: C203.2, IC8.6, R171.2, R172.1, R174.1
unnamed: C199.+, R163.2
OLED-DC: P1.15, U1.47
OLED-RES: P1.16, U1.43
OUT1-L: J4.TB, P3.1
OUT1-LP: C115.-, P3.2, R97.1
OUT1-R: J5.TB, P3.3
OUT1-RP: C109.-, P3.4, R89.1
OUT1L+: R91.2, U14.36
OUT1L-: R90.2, U14.37
OUT1R+: R83.2, U14.38
OUT1R-: R82.2, U14.39
OUT2-L: C131.-, J11.TB, R107.1
OUT2-R: C119.-, J12.TB, R100.1
OUT2L+: R102.2, U14.40
OUT2L-: R101.2, U14.41
OUT2R+: R45.2, U14.42
OUT2R-: R44.2, U14.43
POWER_CON: R162.2, U1.134
POWER_ON: J10.0, R162.1, U6.7, U21.5
POWER_SW: J10._0, U1.136
RD: U1.44, U3.28
RFS0: DSP1.P$75, R168.1, U14.29
RSCLK0: DSP1.P$76, R167.1, U14.28
SA10: DSP1.P$164, U9.22
SCAS_: DSP1.P$166, U9.17
SCKE: DSP1.P$173, U9.37
SCL: J1.3, R66.2, U1.123
SDA: J1.2, R65.2, U1.122
SMS_: DSP1.P$172, U9.19
SPI1-CS0: P1.17, U1.56
SPI1-CS1: P1.18, U1.62
SPI1-CS2: R9.1, U1.64, U$6.1
SPI1-MISO: P1.20, R11.1, U1.60, U$6.7
SPI1-MOSI: P1.21, R10.1, U1.58, U$6.2
SPI1-SCK: P1.22, R12.1, U1.57, U$6.5
SRAS_: DSP1.P$167, U9.18
SW0: U1.21, U20.4
SW0CON^: J7.T, R38.1, R39.2
SW1: U1.22, U20.6
SW1CON^: J6.T, R40.1, R41.2
SWE_: DSP1.P$165, U9.16
TCK: DSP1.P$94, JP8.8
TDI: DSP1.P$86, JP8.12
TDO: DSP1.P$87, R50.1
TFS0: DSP1.P$69, R168.2, U14.22
TFS1: DSP1.P$60, U17.13
TMS: DSP1.P$85, JP8.6
TRST_: DSP1.P$84, JP8.10, R70.1
TSCLK0: DSP1.P$72, R167.2, U14.21
TSCLK1: DSP1.P$61, U17.12
UNREG_IN: C43.2, C44.2, C175.+, D1.C, R63.2, U6.2, U21.7
USB-OC: R19.1, U1.66, U4.5
USB-VBOF: R20.1, U1.74, U4.4
VBUS: C50.2, C51.+, J8.1, U1.68, U4.6, U4.7, U4.8
VDDCORE: C23.1, C24.1, C25.1, C26.1, C27.1, C28.1, C29.1, C30.1, C31.1, C40.1, R6.2, U1.29, U1.51, U1.55, U1.138
VDDEXT: C76.+, C77.+, C78.+, C79.2, C80.2, C81.2, C82.2, C83.2, C84.2, C85.2, C86.2, C87.2, C88.2, DSP1.P$6, DSP1.P$12, DSP1.P$18, DSP1.P$20, DSP1.P$31, DSP1.P$45, DSP1.P$57, DSP1.P$71, DSP1.P$93, DSP1.P$107, DSP1.P$118, DSP1.P$134, DSP1.P$145, DSP1.P$156, DSP1.P$171, R25.1, R27.1
VDDIN: C15.1, C16.1, C17.1, R17.1, U1.17
VDDINT: C89.2, C90.2, C91.2, C92.2, C93.2, C94.2, DSP1.P$25, DSP1.P$52, DSP1.P$66, DSP1.P$80, DSP1.P$111, DSP1.P$143, DSP1.P$157, DSP1.P$168, R24.1, VDDINT.TP
VDDIO: C4.1, C5.1, C6.1, C7.1, C8.1, C9.1, C10.1, C11.1, C12.1, C13.1, C14.1, R16.1, U1.7, U1.36, U1.69, U1.81, U1.92, U1.93, U1.108, U1.116
VDDOUT: C18.1, C19.1, R6.1, R7.1, U1.16, VDDOUT.TP
VDDSYS: C20.1, C21.1, C22.1, R7.2, U1.84
VREF: IC2.3, IC2.5, IC5.3, IC5.5, IC6.3, IC6.5, IC7.1, IC7.2, IC7.5, IC8.3, IC8.5, R81.2, R84.2, R108.2, R109.2, R131.2, R132.2
VROUT: DSP1.P$4, DSP1.P$5, U18.4
WE: U1.42, U3.11
